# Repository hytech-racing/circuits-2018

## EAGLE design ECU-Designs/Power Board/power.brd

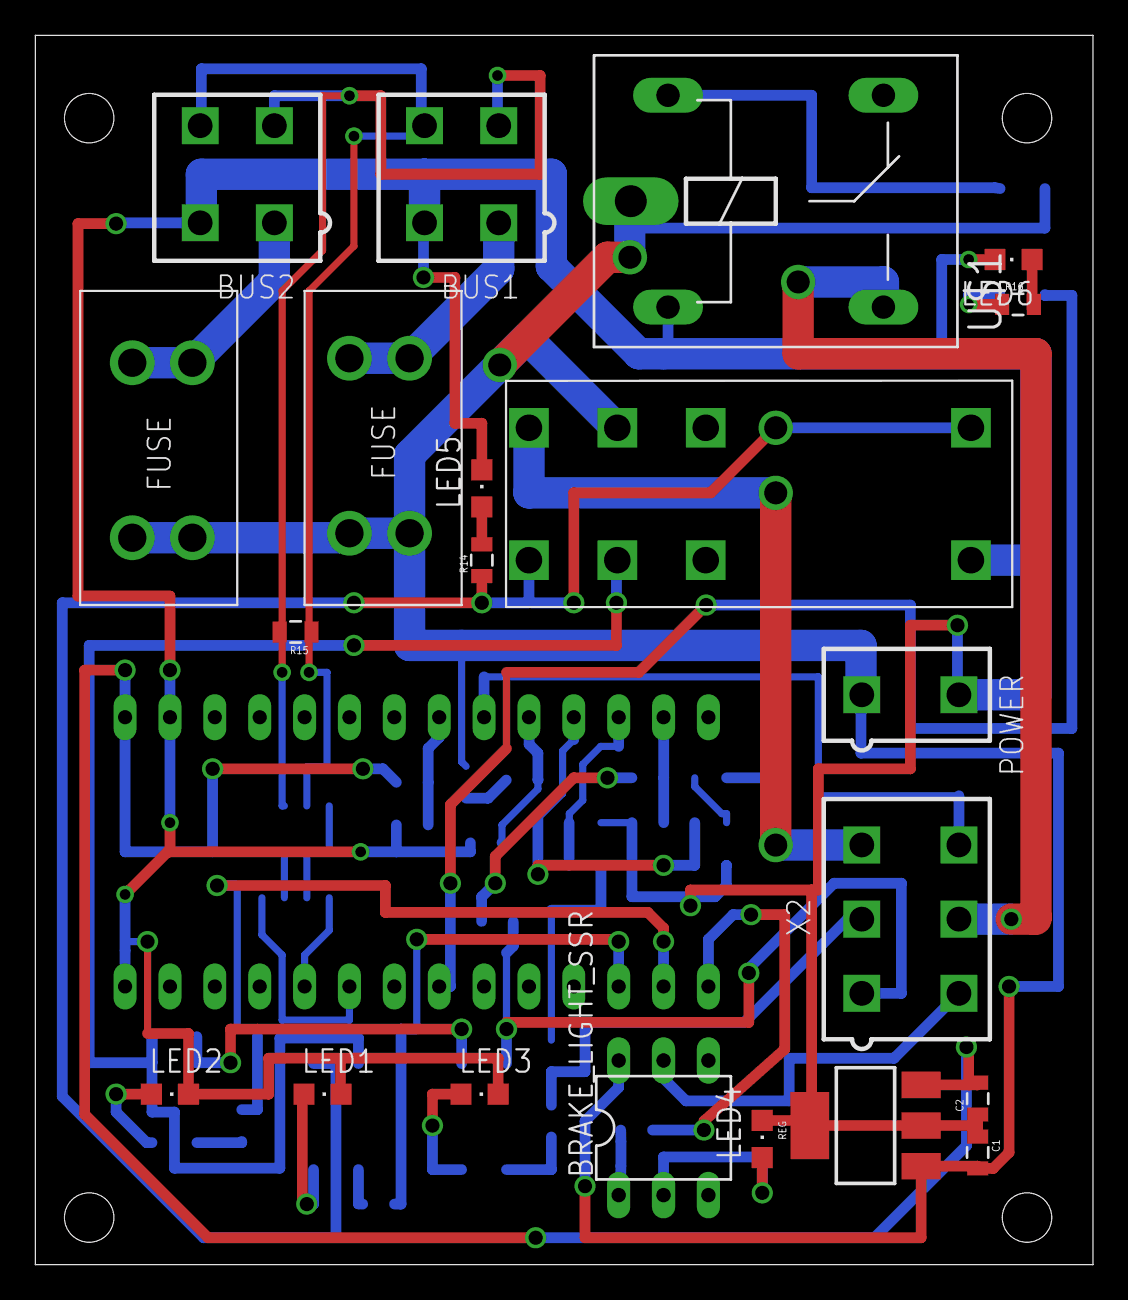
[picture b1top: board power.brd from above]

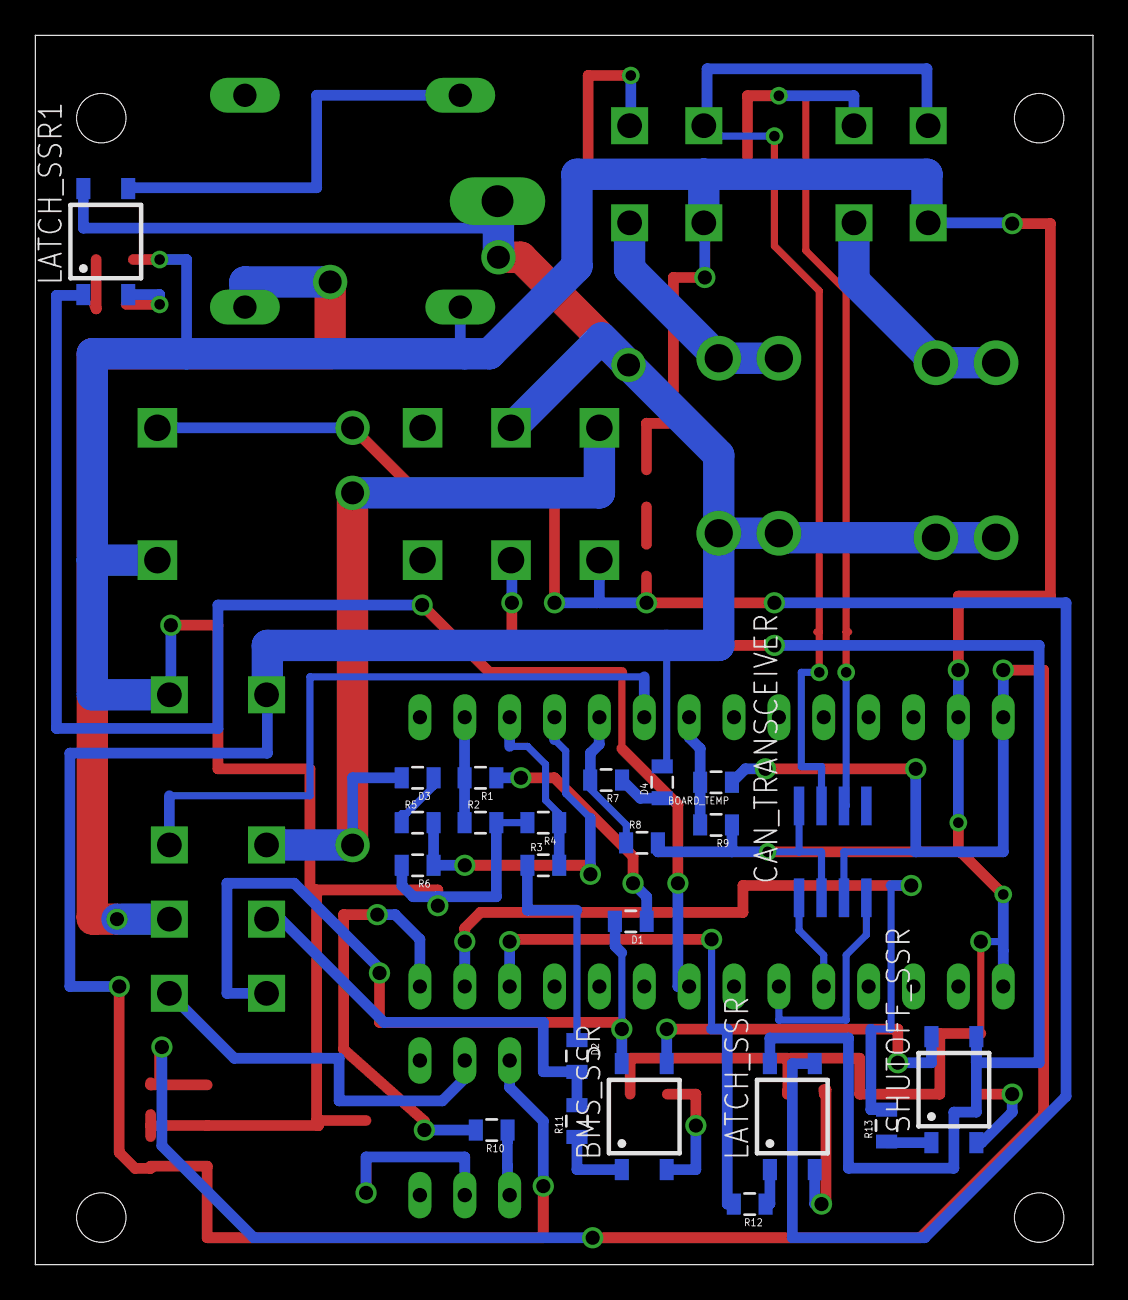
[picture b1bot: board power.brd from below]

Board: 2 copper layers, 59.9 x 69.6 mm, 45 parts (23 on the bottom side), 43 nets.

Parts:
BMS_SSR: CPC1002N; SOP04
BOARD_TEMP: THERMISTOR_NCP21; 0805
BRAKE_LIGHT_SSR: SOLID_STATE_RELAY_VO14642AT; DIL06
BUS1, BUS2: MINIFIT_5566-4
C1: .22uF; 0805
C2: .1uF; 0805
CAN_TRANSCEIVER: MCP2551; SOIC-08
D1, D2, D3, D4: DIODE_0805; 0805
FUSE_BUS_1, FUSE_BUS_2: 5A; FUSE_HOLDER
IMD_SHUTDOWN: DPDT_RELAY_PANASONIC_JW2SN-DC9V; DPDT_RELAY_PANASONIC_JW2SN
LATCH_SSR, LATCH_SSR1: CPC1002N; SOP04
LED1, LED2, LED3, LED4, LED5, LED6: LED-805
POWER: MINIFIT_5566-2
R1, R3, R5, R7: 43k; 0805
R2, R4, R6, R8: 12k; 0805
R9: 10k; 0805
R10, R11, R12, R13, R16: 100; 0805
R14: 430; 0805
R15: 120; 0805
REG: 5V; SOT223
SHUTOFF_SSR: CPC1002N; SOP04
U$1: ORWH-SH-112D1F; ZF112
U$3: TEENSY_3.2_SIMPLE
X2: MINIFIT_5566-6

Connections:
5VSUPPLY: BOARD_TEMP.1, C2.2, CAN_TRANSCEIVER.3, REG.3, U$3.VIN
12VSUPPLY: BRAKE_LIGHT_SSR.6, C1.2, D4.2, FUSE_BUS_1.R1, FUSE_BUS_1.R2, FUSE_BUS_2.L1, FUSE_BUS_2.L2, IMD_SHUTDOWN.6, LATCH_SSR1.4, POWER.1, REG.1, U$1.P
12VSUPPLY_READ: R7.2, R8.1, U$3.A3
BMS_OK: D2.2, R11.2, X2.2
BMS_OK_READ: R3.2, R4.1, U$3.A1
CANH: BUS1.4, BUS2.4, CAN_TRANSCEIVER.7, R15.1
CANL: BUS1.3, BUS2.3, CAN_TRANSCEIVER.6, R15.2
GND: BUS1.2, BUS2.2, C1.1, C2.1, CAN_TRANSCEIVER.2, CAN_TRANSCEIVER.8, IMD_SHUTDOWN.COIL+, LED1.C, LED2.C, LED3.C, LED4.C, LED5.C, LED6.C, POWER.2, R2.2, R4.2, R6.2, R8.2, R9.1, REG.2, REG.4, U$1.2, U$3.AGND, U$3.GND
INVERTER_SUPPLY: U$1.S, X2.5
unnamed: LATCH_SSR.2, LED1.A
unnamed: CAN_TRANSCEIVER.4, U$3.D4(CANRX)
unnamed: CAN_TRANSCEIVER.1, U$3.D3(CANTX)
unnamed: BRAKE_LIGHT_SSR.5, X2.4
unnamed: R12.2, U$3.D10(TX2)
unnamed: IMD_SHUTDOWN.4, IMD_SHUTDOWN.COIL-, LATCH_SSR.3, R14.1
unnamed: BRAKE_LIGHT_SSR.2, LED4.A
unnamed: LATCH_SSR.1, R12.1
unnamed: BMS_SSR.2, LED3.A
unnamed: BUS1.1, FUSE_BUS_1.L1, FUSE_BUS_1.L2
unnamed: BUS2.1, FUSE_BUS_2.R1, FUSE_BUS_2.R2
unnamed: R13.1, SHUTOFF_SSR.1
unnamed: R10.2, U$3.D12
unnamed: R13.2, U$3.D11
unnamed: BOARD_TEMP.2, R9.2, U$3.A5
unnamed: LED2.A, SHUTOFF_SSR.2
unnamed: BRAKE_LIGHT_SSR.1, R10.1
unnamed: BMS_SSR.1, R11.1
unnamed: LED5.A, R14.2
unnamed: U$3.A4, X2.6
unnamed: LATCH_SSR1.1, U$3.D6
unnamed: D1.1, R1.1
unnamed: D2.1, R3.1
unnamed: D3.1, R5.1
unnamed: D4.1, R7.1
unnamed: LATCH_SSR1.3, U$1.1
unnamed: LATCH_SSR1.2, R16.1
unnamed: LED6.A, R16.2
OKHS_1: BMS_SSR.4, D1.2, X2.1
OKHS_2: BMS_SSR.3, SHUTOFF_SSR.4
OKHS_3: IMD_SHUTDOWN.3, LATCH_SSR.4, SHUTOFF_SSR.3
OKHS_READ: R1.2, R2.1, U$3.A0
SHUTDOWN_OUT: D3.2, IMD_SHUTDOWN.5, X2.3
SHUTDOWN_OUT_READ: R5.2, R6.1, U$3.A2

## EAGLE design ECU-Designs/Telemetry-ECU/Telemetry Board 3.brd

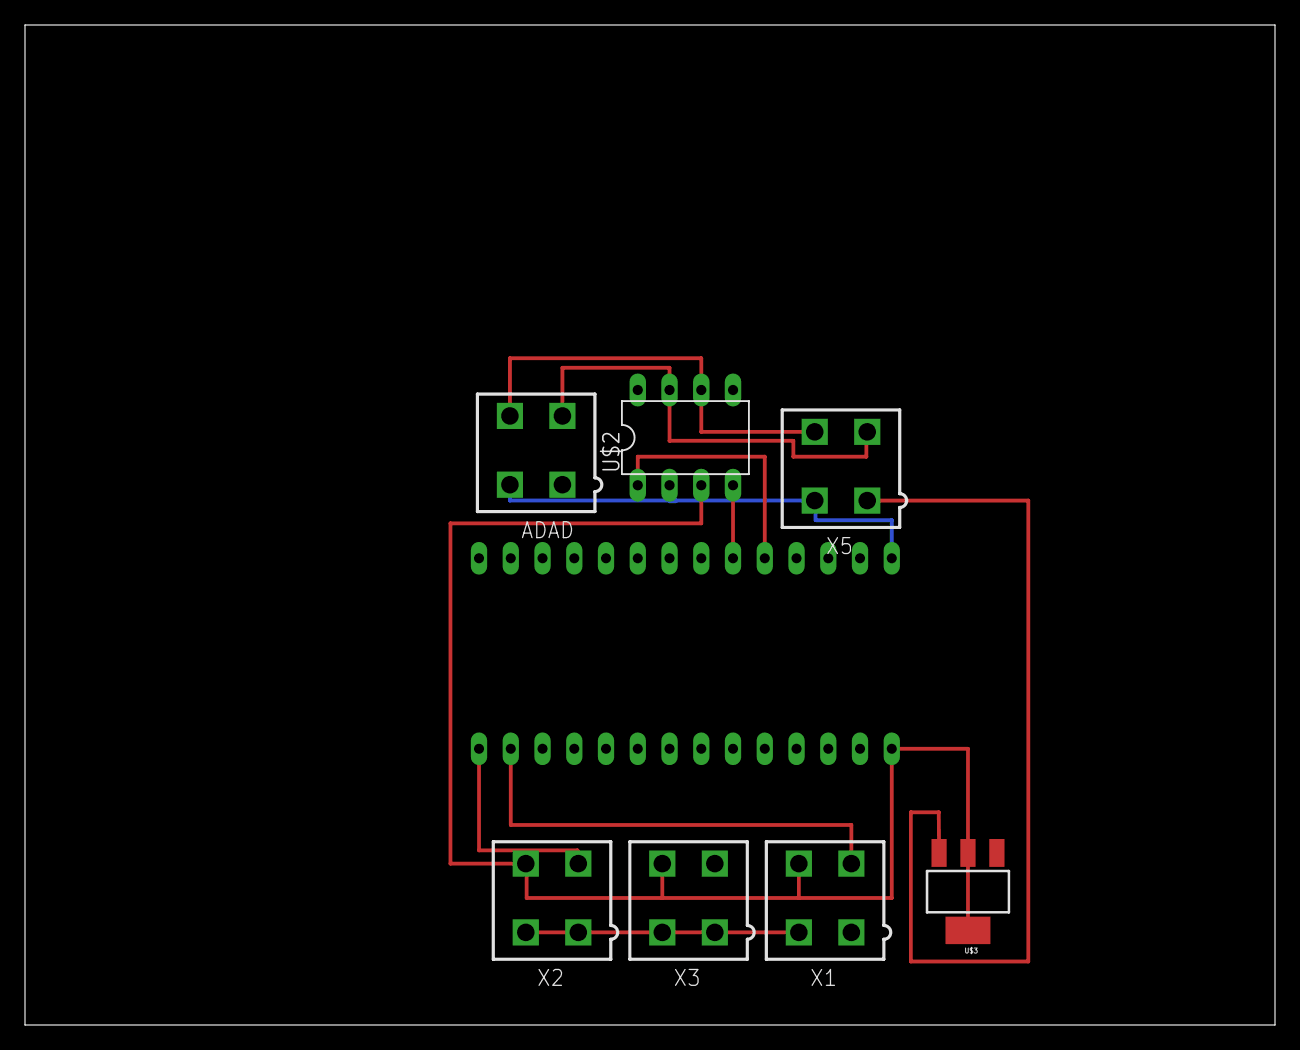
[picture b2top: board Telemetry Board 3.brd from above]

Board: 2 copper layers, 100.0 x 80.0 mm, 8 parts (0 on the bottom side), 9 nets.

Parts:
ADAD: MINIFIT_5566-4
U$1: TEENSY_3.2_SIMPLE
U$2: MCP2551; DIL08
U$3: SOT223
X1: Suspension Sensor; MINIFIT_5566-4
X2: Wheel Sensor; MINIFIT_5566-4
X3: Tire Temperature Sensor; MINIFIT_5566-4
X5: MINIFIT_5566-4

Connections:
unnamed: ADAD.1, U$3.3, X5.1
unnamed: ADAD.3, U$2.7, X5.3
unnamed: ADAD.4, U$2.6, X5.4
unnamed: ADAD.2, U$1.GND, U$2.2, U$3.1, X1.2, X2.2, X3.2, X5.2
unnamed: U$1.D3(CANTX), U$2.1
unnamed: U$1.D4(CANRX), U$2.4
unnamed: U$1.VIN, U$2.3, U$3.2, U$3.4, X1.4, X2.4, X3.4
unnamed: U$1.D13, X2.3
unnamed: U$1.A0, X1.3

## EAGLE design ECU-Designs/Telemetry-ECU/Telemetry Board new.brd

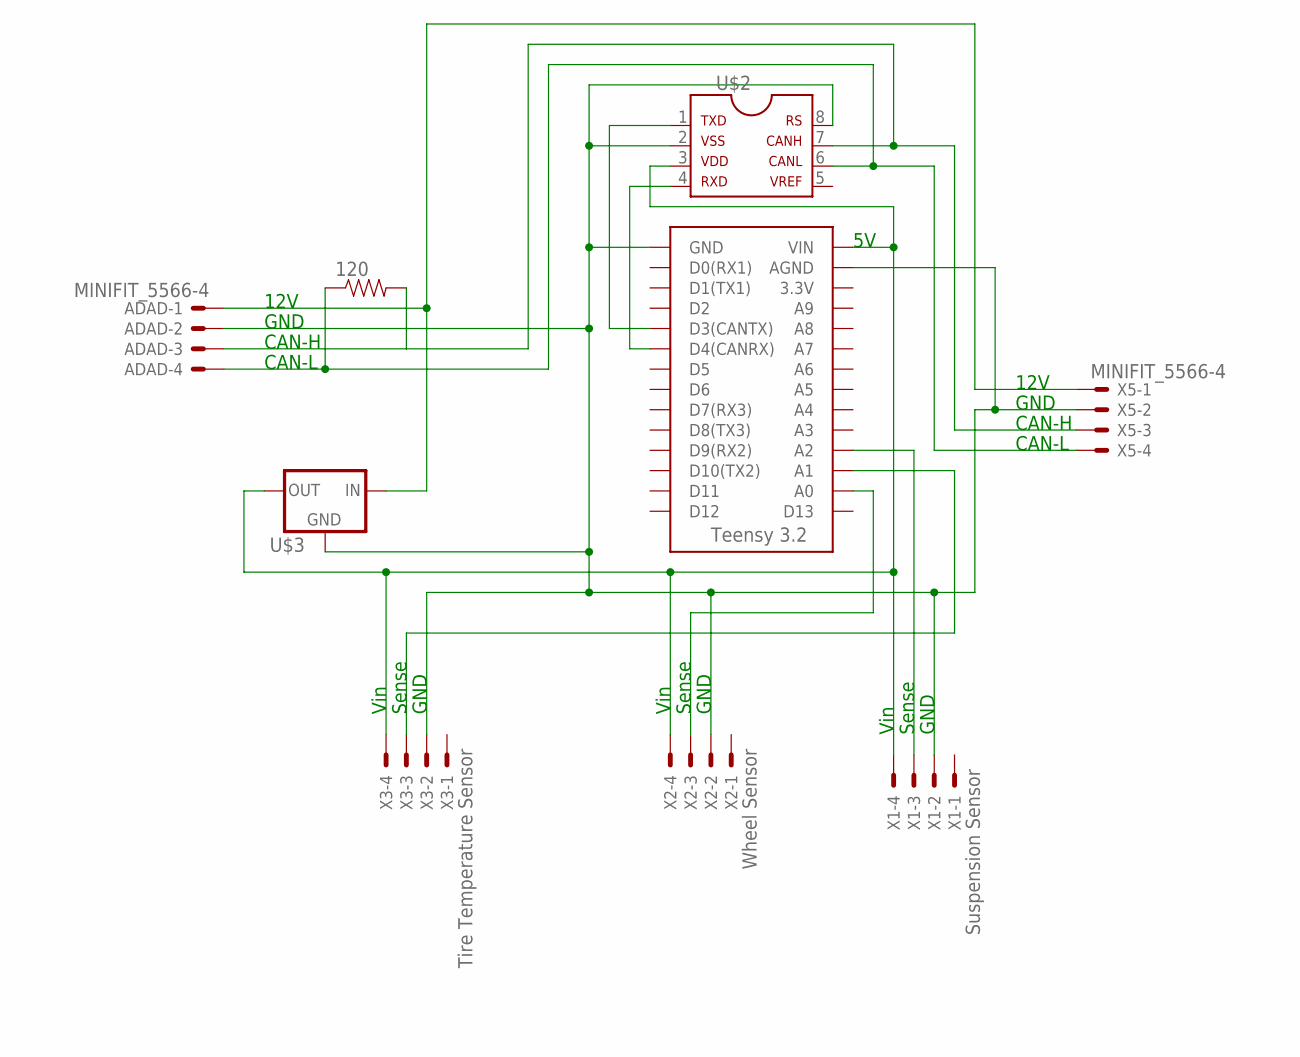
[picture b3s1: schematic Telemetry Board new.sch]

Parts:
120: RESISTOR0402; 0402-RES
ADAD: MINIFIT_5566-4
U$1: TEENSY_3.2_SIMPLE
U$2: MCP2551SOIC; SOIC08
U$3: 5V_REGULATOR_LM340-NLM340MPX-5.0/NOPB; SOT223
X1: Suspension Sensor; MINIFIT_5566-4
X2: Wheel Sensor; MINIFIT_5566-4
X3: Tire Temperature Sensor; MINIFIT_5566-4
X5: MINIFIT_5566-4

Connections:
unnamed: ADAD.1, U$3.1 (IN), X5.1
unnamed: 120.2, ADAD.3, U$2.7, X5.3
unnamed: 120.1, ADAD.4, U$2.6, X5.4
unnamed: ADAD.2, U$1.AGND, U$1.GND, U$2.2, U$2.8, U$3.2 (GND), U$3.4 (GND), X1.2, X2.2, X3.2, X5.2
unnamed: U$1.D3(CANTX), U$2.1
unnamed: U$1.D4(CANRX), U$2.4
unnamed: U$1.A1, X3.3
unnamed: U$1.VIN, U$2.3, U$3.3 (OUT), X1.4, X2.4, X3.4
unnamed: U$1.A0, X2.3
unnamed: U$1.A2, X1.3

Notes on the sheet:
GND
12V
CAN-H
CAN-L
Vin
Sense

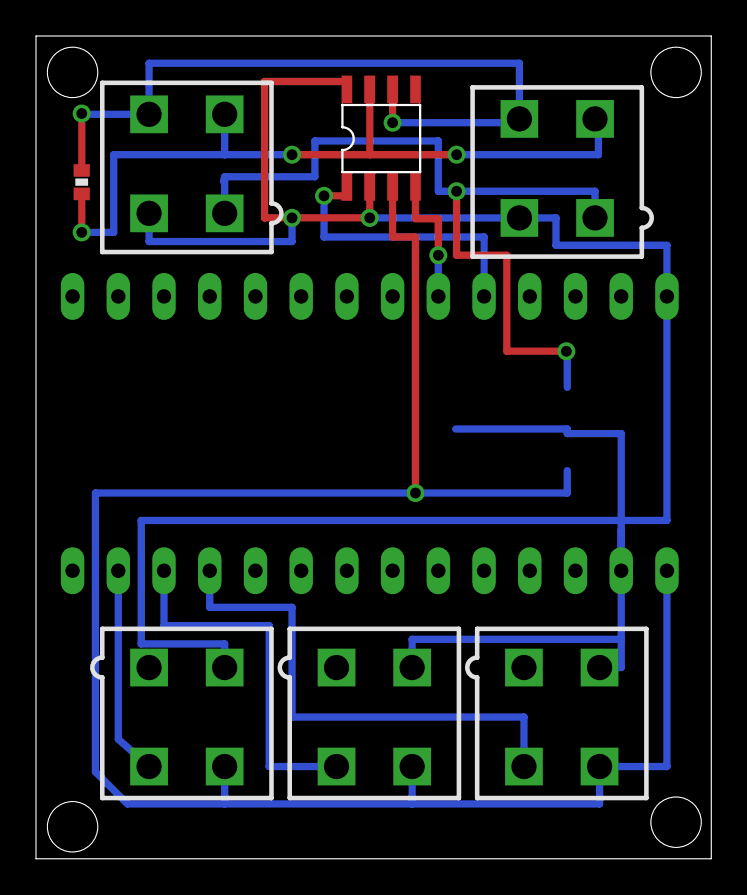
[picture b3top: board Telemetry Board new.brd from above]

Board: 2 copper layers, 37.5 x 45.7 mm, 9 parts (1 on the bottom side), 10 nets.

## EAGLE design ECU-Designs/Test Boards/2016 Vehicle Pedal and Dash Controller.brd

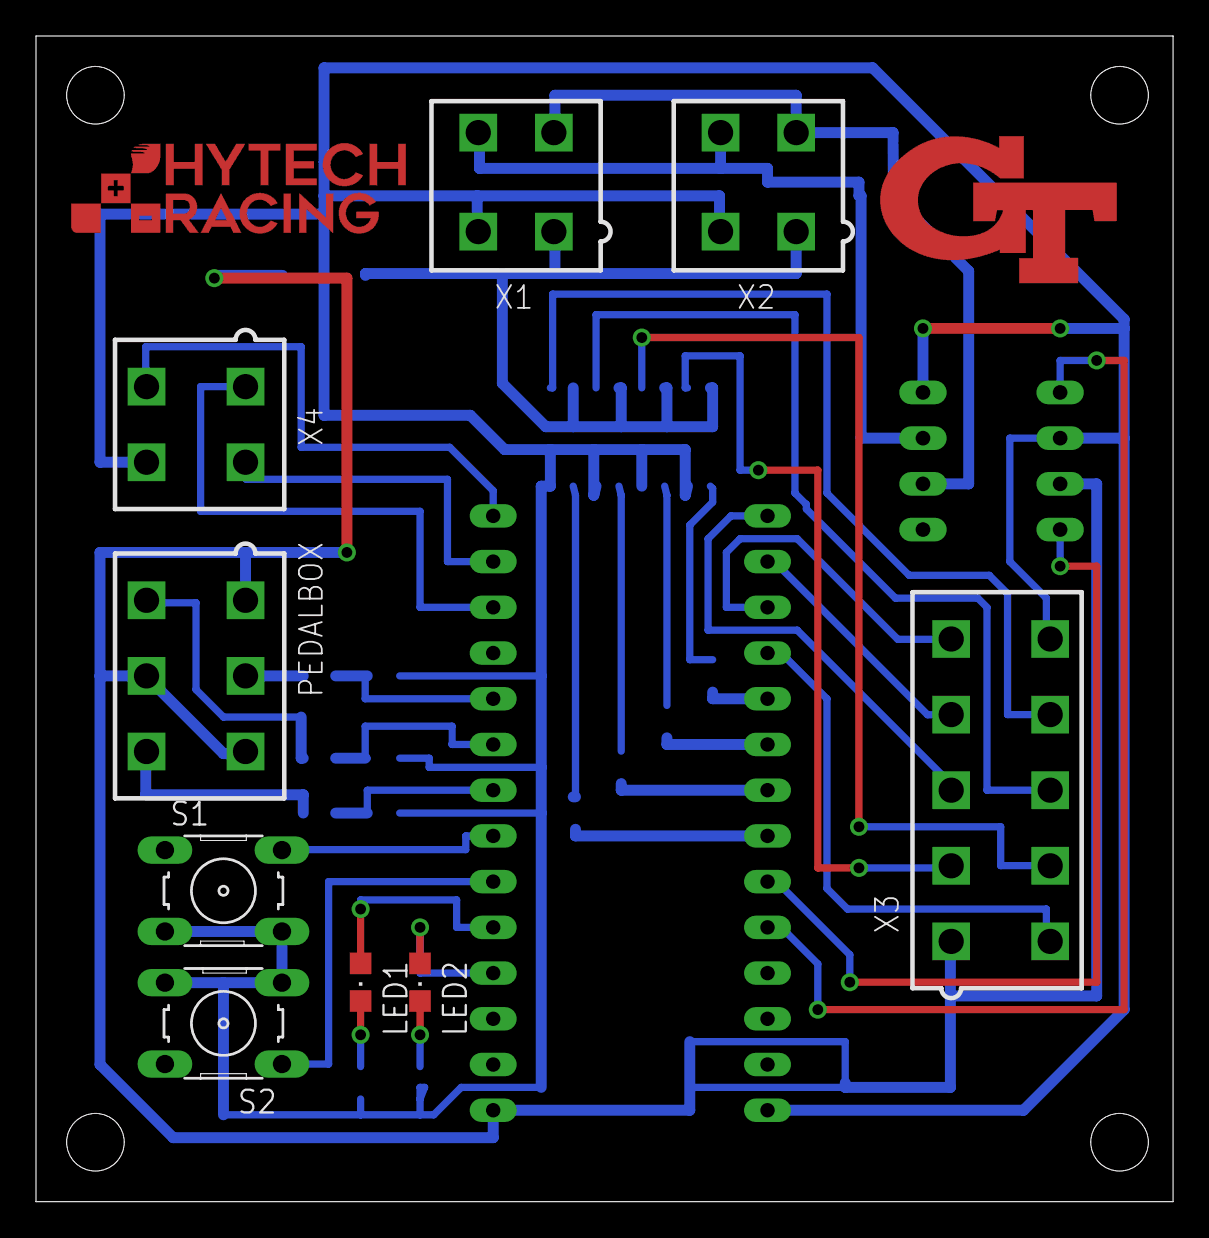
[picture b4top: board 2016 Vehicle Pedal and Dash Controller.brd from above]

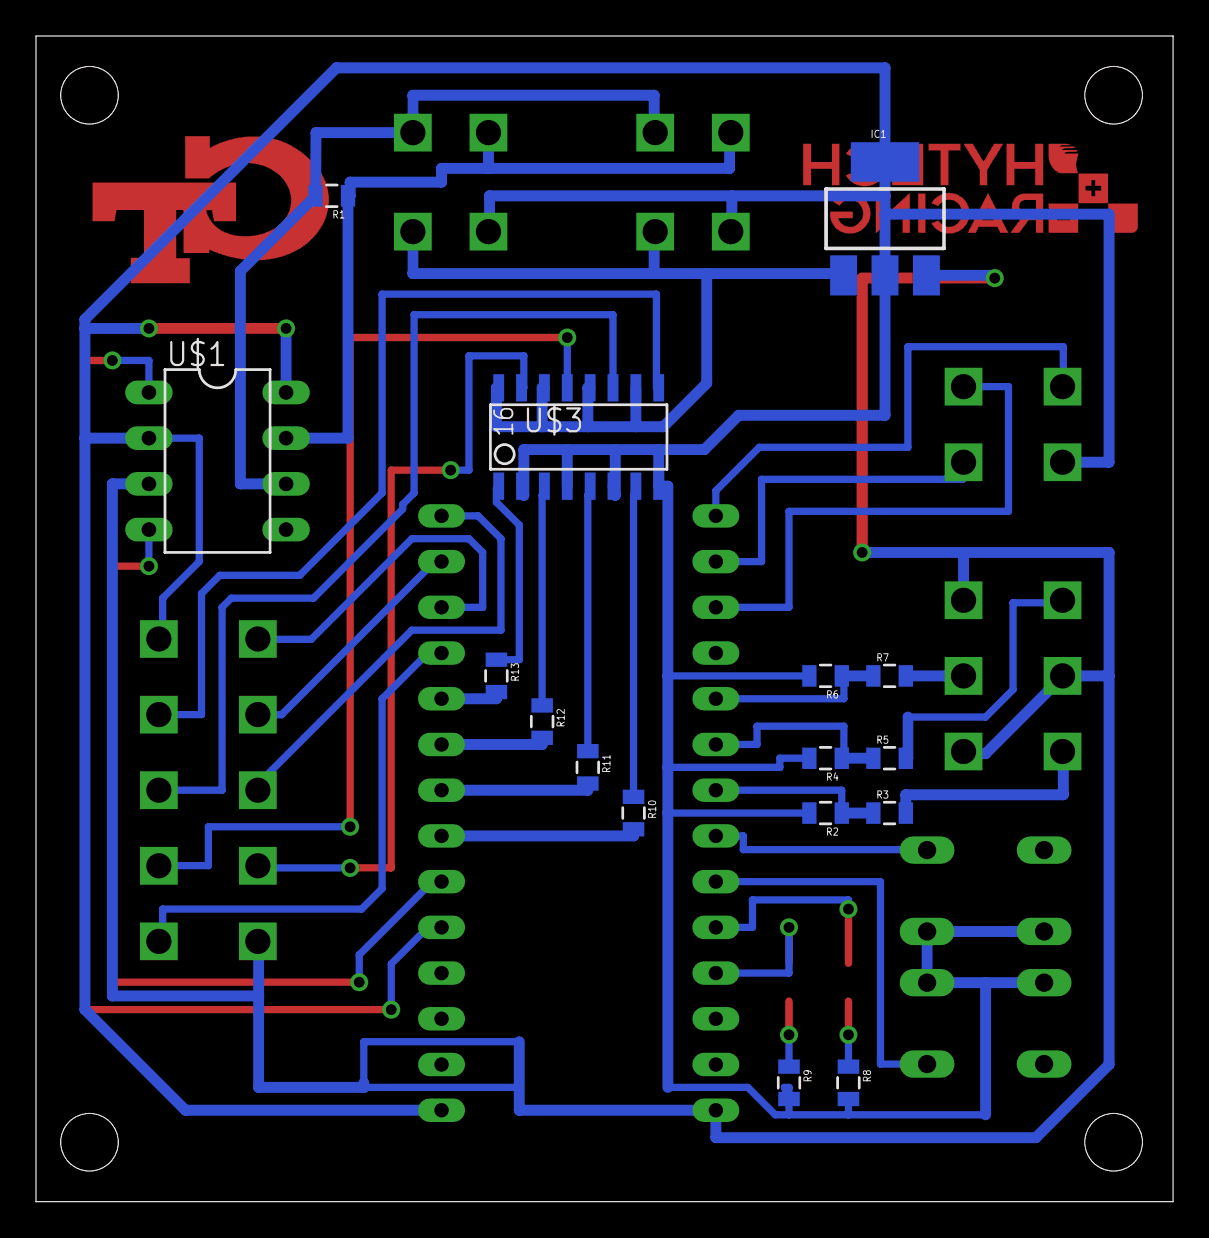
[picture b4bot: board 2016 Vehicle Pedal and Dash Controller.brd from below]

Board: 2 copper layers, 63.2 x 64.8 mm, 26 parts (16 on the bottom side), 38 nets.

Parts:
IC1: SOT223
LED1, LED2: LED-805
PEDALBOX: MINIFIT_5566-6
R1: 120; 0805
R2, R4, R6: 20k; 0805
R3, R5, R7, R10, R11, R12, R13: 10k; 0805
R8, R9: 330; 0805
S1, S2: B3F-10XX
U$1: MCP2551DIL; DIL08
U$2: TEENSY_3.2_SIMPLE
U$3: TLP291-4; SOIC-16
X1, X2, X4: MINIFIT_5566-4
X3: MINIFIT_5566-10

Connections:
12VSUPPLY: IC1.1, U$3.10, U$3.12, U$3.14, U$3.16, X1.1, X2.1
CANH: R1.1, U$1.7, X1.4, X2.4
CANL: R1.2, U$1.6, X1.3, X2.3
GND: IC1.2, IC1.4, R2.2, R4.2, R6.2, R8.2, R9.2, S1.3, S1.4, S2.3, S2.4, U$1.2, U$1.8, U$2.GND, U$3.2, U$3.4, U$3.6, U$3.8, X1.2, X2.2, X3.10, X4.4
unnamed: U$2.D12, X3.3
unnamed: IC1.3, PEDALBOX.1, PEDALBOX.3, PEDALBOX.5, U$1.3, U$2.VIN, X3.1
unnamed: PEDALBOX.6, R3.2
unnamed: PEDALBOX.4, R5.2
unnamed: U$1.1, U$2.D3(CANTX)
unnamed: U$1.4, U$2.D4(CANRX)
unnamed: PEDALBOX.2, R7.2
unnamed: R2.1, R3.1, U$2.A5
unnamed: R4.1, R5.1, U$2.A4
unnamed: R6.1, R7.1, U$2.A3
unnamed: U$2.D11, X3.4
unnamed: U$2.D10(TX2), X3.5
unnamed: U$2.D9(RX2), X3.6
unnamed: R13.2, U$2.D8(TX3)
unnamed: U$3.9, X3.9
unnamed: U$3.11, X3.8
unnamed: U$3.13, X3.7
unnamed: U$3.15, X3.2
unnamed: R12.2, U$2.D7(RX3)
unnamed: R11.2, U$2.D6
unnamed: R10.2, U$2.D5
unnamed: S1.2, U$2.A6
unnamed: S2.1, U$2.A7
unnamed: LED1.A, U$2.A8
unnamed: LED2.A, U$2.A9
unnamed: LED1.C, R8.1
unnamed: LED2.C, R9.1
unnamed: U$2.D13, X4.3
unnamed: U$2.A0, X4.2
unnamed: U$2.A1, X4.1
unnamed: R11.1, U$3.5
unnamed: R12.1, U$3.3
unnamed: R13.1, U$3.1
unnamed: R10.1, U$3.7

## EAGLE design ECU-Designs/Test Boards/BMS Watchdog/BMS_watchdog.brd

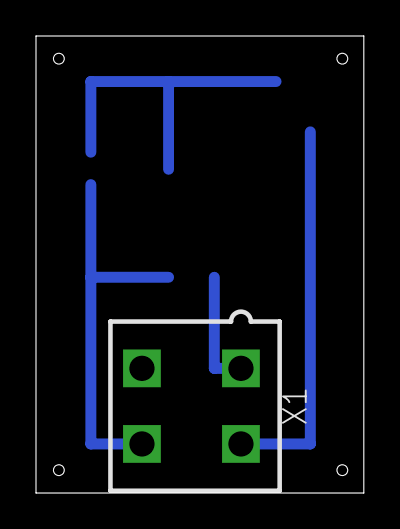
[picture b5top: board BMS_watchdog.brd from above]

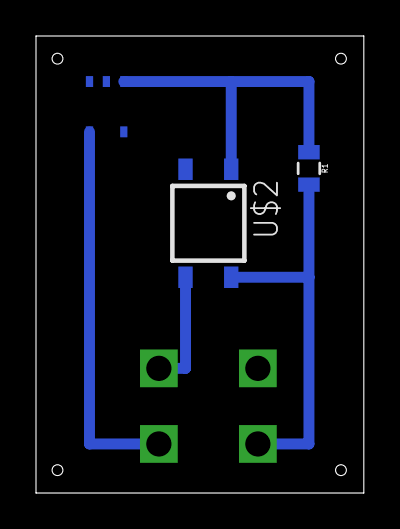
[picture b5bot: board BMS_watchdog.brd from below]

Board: 2 copper layers, 18.2 x 25.4 mm, 4 parts (3 on the bottom side), 4 nets.

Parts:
R1: 0805
U$1: STWD100; SOT23-5
U$2: CPC1002N; SOP04
X1: MINIFIT_5566-4

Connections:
unnamed: R1.2, U$2.4, X1.4
unnamed: U$1.WDI, X1.2
unnamed: R1.1, U$1.WDO, U$2.1
unnamed: U$2.3, X1.1

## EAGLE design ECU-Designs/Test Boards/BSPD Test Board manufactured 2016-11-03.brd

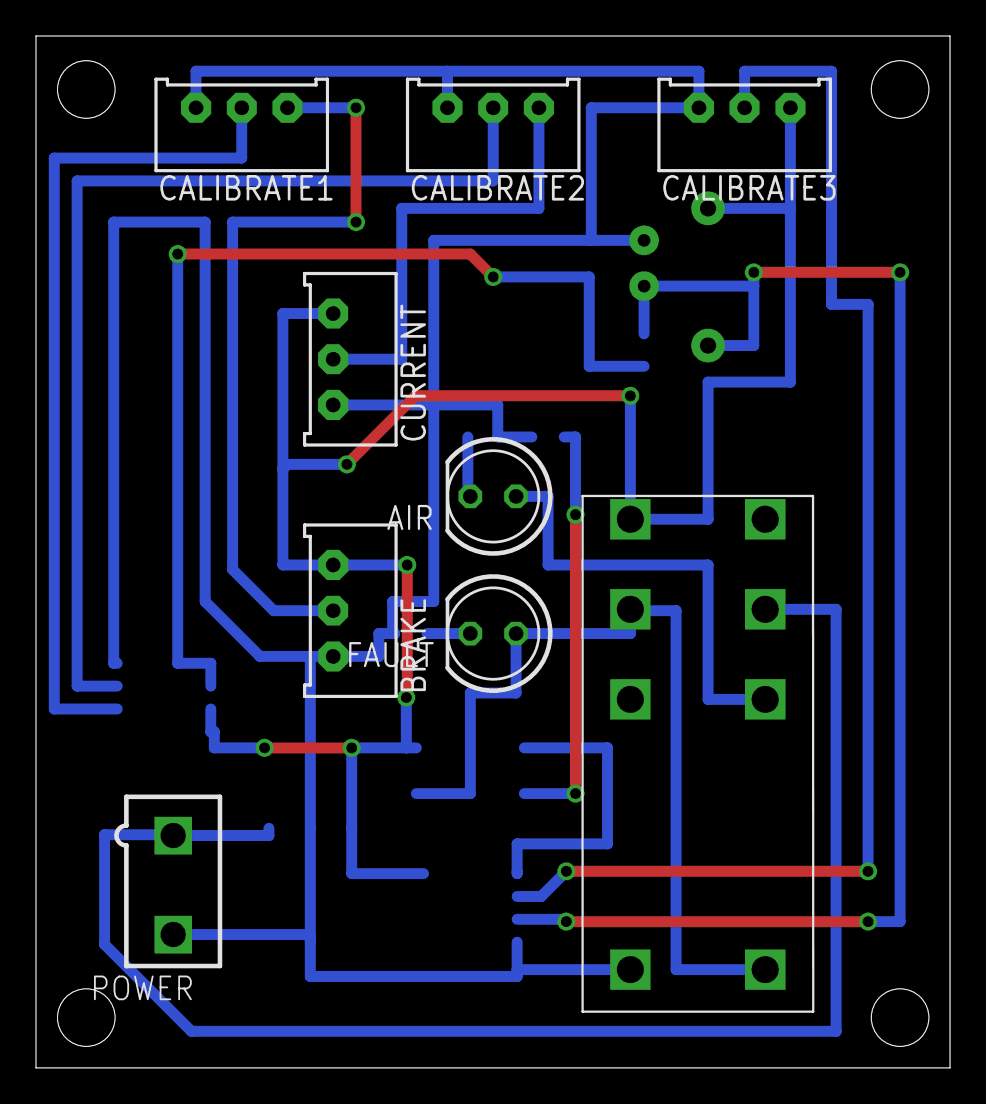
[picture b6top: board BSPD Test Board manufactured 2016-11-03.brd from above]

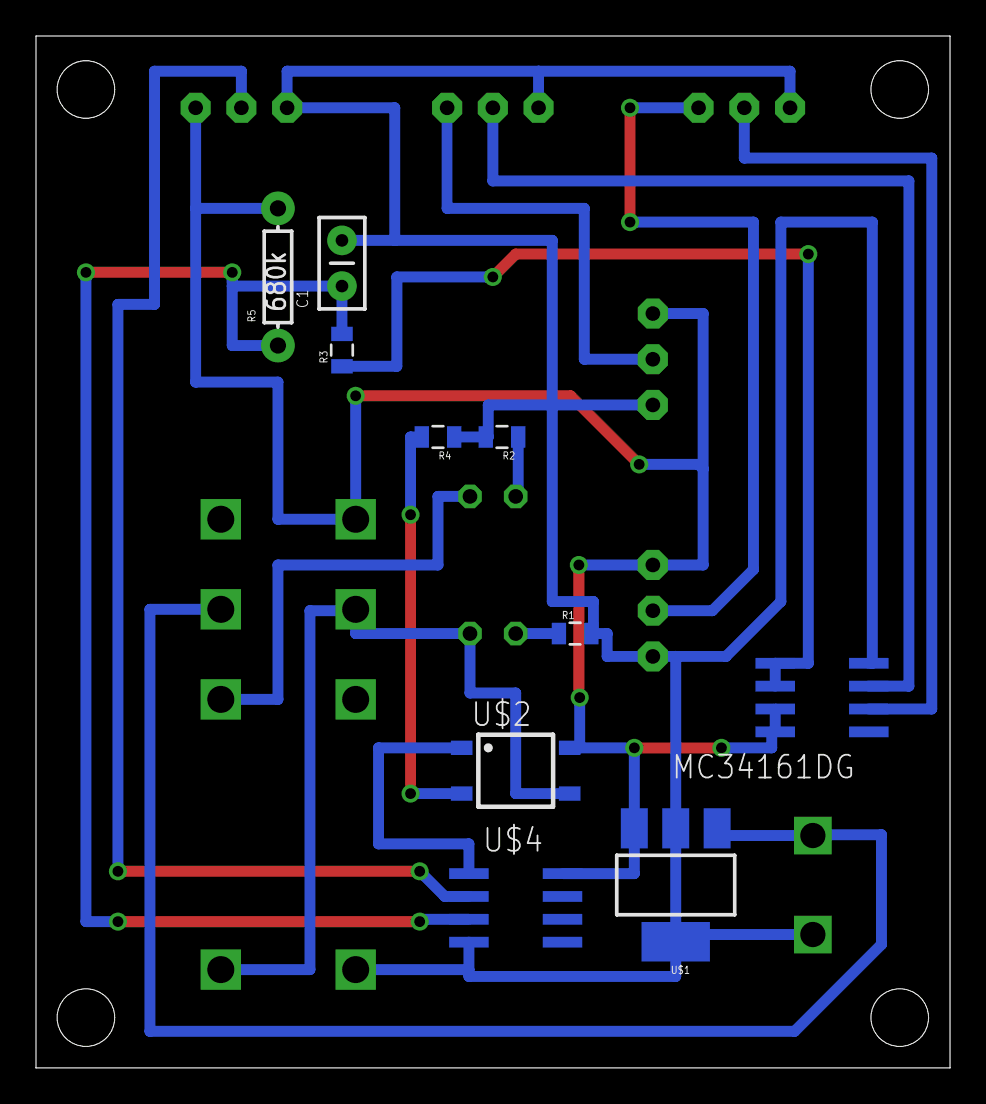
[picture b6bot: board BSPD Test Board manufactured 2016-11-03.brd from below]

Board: 2 copper layers, 50.8 x 57.3 mm, 19 parts (10 on the bottom side), 16 nets.

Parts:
AIR: LED-5MM
BRAKE: TRIMPOT_3296
C1: .47u; CAP-PTH-SMALLEZ
CALIBRATE1, CALIBRATE2, CALIBRATE3: TRIMPOT_3296
CURRENT: TRIMPOT_3296
FAULT: LED-5MM
MC34161DG: SOIC-08
POWER: MINIFIT_5566-2
R1, R3: 330; 0805
R2: 680; 0805
R4: 430; 0805
R5: 680k; AXIAL-0.3EZ
U$1: SOT223
U$2: CPC1002N; SOP04
U$3: DPDT_RELAY_PANASONIC_JW2SN-DC5V; DPDT_RELAY_PANASONIC_JW2SN
U$4: LM293DG4; SOIC-08

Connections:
5VSUPPLY: BRAKE.1, CALIBRATE3.1, CURRENT.1, MC34161DG.7, MC34161DG.8, R5.P$2, U$1.3, U$2.4, U$3.4, U$4.8
12VSUPPLY: POWER.1, U$1.1, U$3.6
FAULT_INDICATE: FAULT.A, U$2.3, U$3.3, U$3.COIL-
GND: BRAKE.3, C1.2, CALIBRATE1.3, CALIBRATE2.3, CALIBRATE3.3, CURRENT.3, MC34161DG.4, POWER.2, R1.2, R2.2, R4.1, U$1.2, U$1.4, U$3.COIL+, U$4.4
unnamed: BRAKE.2, CALIBRATE1.1
unnamed: CALIBRATE2.1, CURRENT.2
unnamed: CALIBRATE2.2, MC34161DG.3
unnamed: CALIBRATE1.2, MC34161DG.2
unnamed: CALIBRATE3.2, U$4.2
unnamed: FAULT.K, R1.1
unnamed: U$2.1, U$4.1
unnamed: R4.2, U$2.2
unnamed: AIR.A, U$3.7
unnamed: AIR.K, R2.1
unnamed: C1.1, R3.2, R5.P$1, U$4.3
unnamed: MC34161DG.5, MC34161DG.6, R3.1
